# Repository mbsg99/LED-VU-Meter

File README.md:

Visit JLCPCB (https://jlcpcb.com/)

# LED-VU-Meter with JLCPCB
Volume Meter is an Equalizer in the Music systems. In which lights dancing (LEDs) can be seen according to the song, if the song is loud, it reaches its height and stays low in low music.Volume Meter or VU meter PCB design is designed, with the aid of MIC, OP-AMP and LM3914, which glows the LEDs according to sound power, if sound is small, less LEDs will glow, and if sound is High more LEDs will glow, it will also serve as a volume measuring instrument.

# Components Required:
1. Op-amp LM358 and, LM3914 (10 bit comparator),
2. 100KΩ resistor (2 pieces), 1K Ω resistor (3 pieces), 10KΩ resistor, 47KΩ pot,
3. 100nF capacitor (2 pieces), 1000µF capacitor, 10 LEDs,
4. Breadboard and some connector wires.

# Ordering the PCBs From JLCPCB
Full Process is shown using Screenshots Step-wise.

Now we have got the PCB design and it’s time to order the PCB’s. For that, you just have to go to JLCPCB.com, and click on “QUOTE NOW” button.

JLCPCB are also sponsor of this project. JLCPCB (ShenzhenJLC Electronics Co., Ltd.), is the largest PCB prototype enterprise in Chinaand a high-tech manufacturer specializing in quick PCB prototype and small-batch PCB production. You can order a minimum of 5 PCBs for just $2.

To get the PCB manufactured, upload the gerber file you downloaded in the last step. Upload the.zip file or you can also drag and drop the gerber files.

After uploading the zip file, you’ll see a success message at the bottom if the file is successfully uploaded.

You can review the PCB in the Gerber viewer to make sure everything is good. You can view both top and bottom of the PCB. After making sure our PCB looks good, we can now place the order at a reasonable price. You can order 5 PCBs for just $2 but if it’s your first order then you can get 5 PCBs for $2.

To place the order, click on “SAVE TO CART” button. My PCBs took 2 days to get manufactured and arrived within a week using DHL delivery option. PCBs were well packed and the quality was really good.

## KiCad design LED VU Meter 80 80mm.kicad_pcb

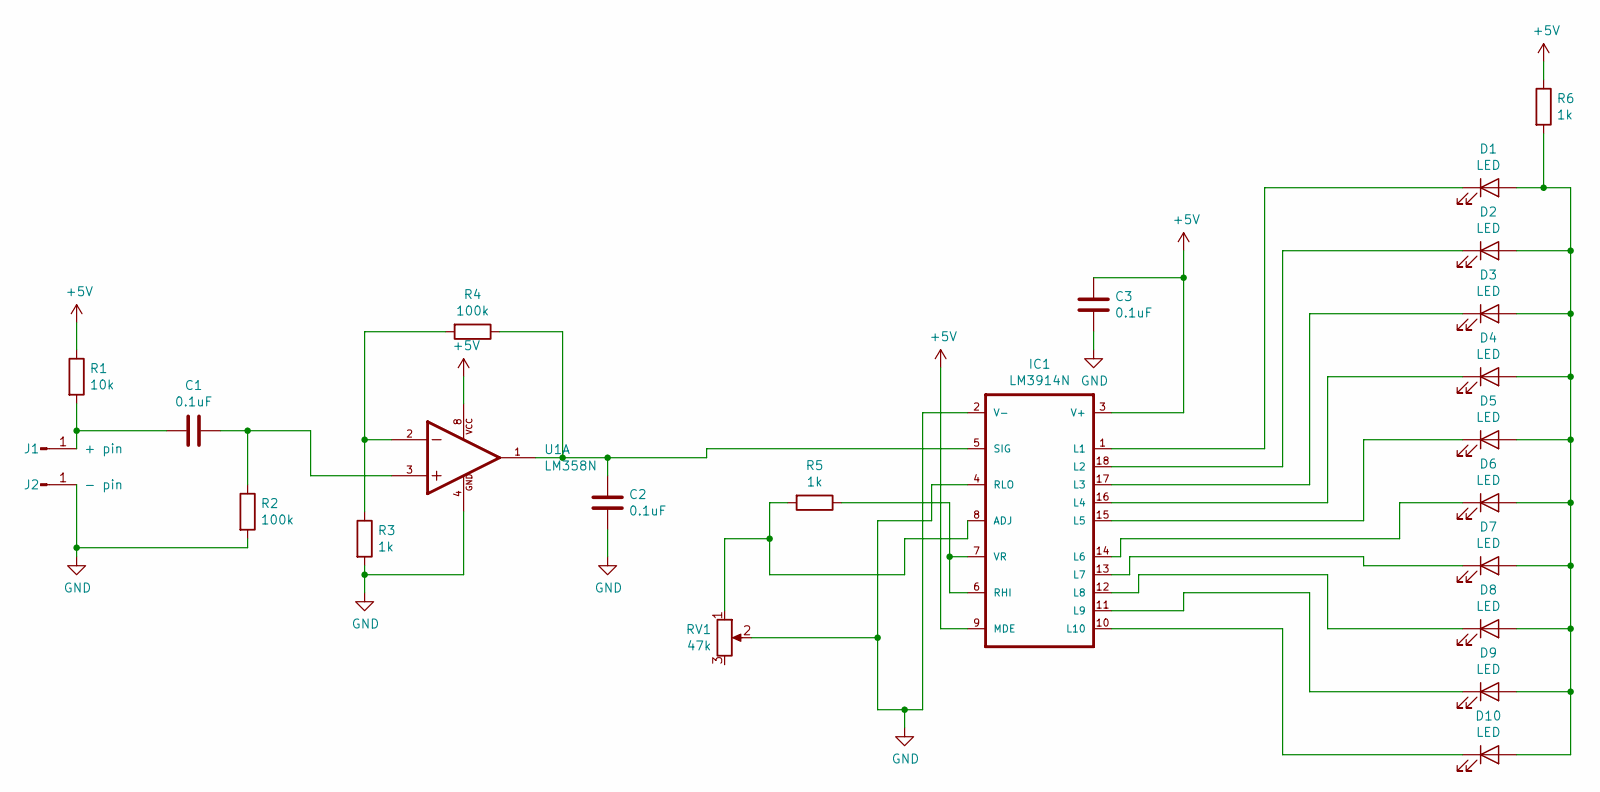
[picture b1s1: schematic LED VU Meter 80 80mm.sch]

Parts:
C1, C2, C3: 0.1uF; CP_Radial_D4.0mm_P1.50mm
D1, D2, D3, D4, D5, D6, D7, D8, D9, D10: LED; LED_D3.0mm
IC1: LM3914N; DIL18
J1: + pin; Pin_D1.0mm_L10.0mm
J2: - pin; Pin_D1.0mm_L10.0mm
R1: 10k; R_Axial_DIN0204_L3.6mm_D1.6mm_P5.08mm_Horizontal
R2, R4: 100k; R_Axial_DIN0204_L3.6mm_D1.6mm_P5.08mm_Horizontal
R3, R5, R6: 1k; R_Axial_DIN0204_L3.6mm_D1.6mm_P5.08mm_Horizontal
RV1: 47k; Potentiometer_ACP_CA6-H2,5_Horizontal
U1: LM358N; DIP762W46P254L960H508Q8

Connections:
+5V: C3.1, IC1.3 (V+), IC1.9 (MDE), R1.1, R6.1, U1.8 (VCC)
GND: C2.2, C3.2, IC1.2 (V-), IC1.4 (RLO), J2.1, R2.2, R3.2, RV1.2, U1.4 (GND)
unnamed: C1.1, R2.1, U1.3 (1IN+)
unnamed: C1.2, J1.1, R1.2
unnamed: C2.1, IC1.5 (SIG), R4.1, U1.1 (1OUT)
unnamed: D1.1 (K), IC1.1 (L1)
unnamed: D1.2 (A), D2.2 (A), D3.2 (A), D4.2 (A), D5.2 (A), D6.2 (A), D7.2 (A), D8.2 (A), D9.2 (A), D10.2 (A), R6.2
unnamed: D2.1 (K), IC1.18 (L2)
unnamed: D3.1 (K), IC1.17 (L3)
unnamed: D4.1 (K), IC1.16 (L4)
unnamed: D5.1 (K), IC1.15 (L5)
unnamed: D6.1 (K), IC1.14 (L6)
unnamed: D7.1 (K), IC1.13 (L7)
unnamed: D8.1 (K), IC1.12 (L8)
unnamed: D9.1 (K), IC1.11 (L9)
unnamed: D10.1 (K), IC1.10 (L10)
unnamed: IC1.6 (RHI), IC1.7 (VR), R5.1
unnamed: IC1.8 (ADJ), R5.2, RV1.1
unnamed: R3.1, R4.2, U1.2 (1IN-)

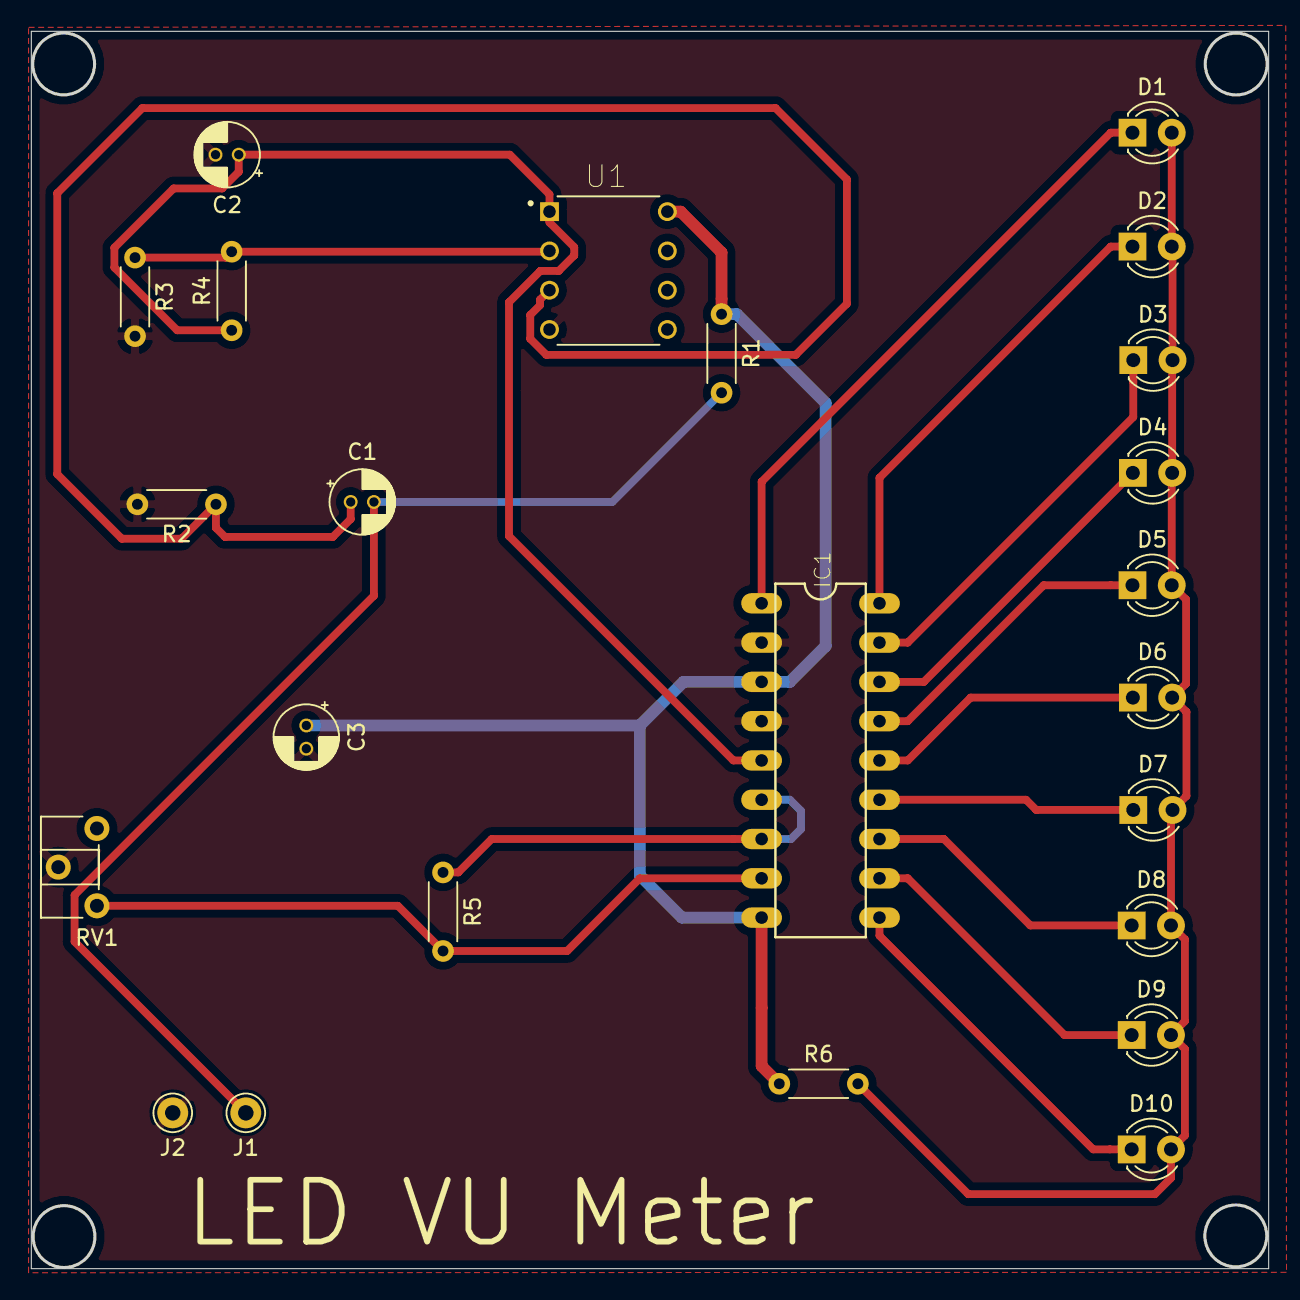
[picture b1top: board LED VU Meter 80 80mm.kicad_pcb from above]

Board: 2 copper layers, 79.9 x 79.9 mm, 24 parts (0 on the bottom side), 19 nets.

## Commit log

2020-08-27 3D Model
2020-08-27 Components Required
2020-08-27 Schematics
2020-08-27 KiCAD file
    Download all the KiCAD Files in a folder
2020-08-27 Create Order PCB on jlcpcb.com Stepwise
2020-08-27 Step-wise Ordering the PCB
2020-08-27 Step 1
